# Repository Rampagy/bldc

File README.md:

# bldc

Open source brushless direct current (permanent magnet alternating current) hardware and software.

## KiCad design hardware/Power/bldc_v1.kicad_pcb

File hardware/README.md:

# Kicad

Version 5.1.2

## Setup

Set Environment Variable `KILOCALLIB` to `path/to/bldc/hardware`.  This allows Kicad to find the custom schematic and footprint libraries:

* infineon.lib
* Interface_RS485.lib
* STM32F4-DISCOVERY-SIMON.lib
* custom.pretty

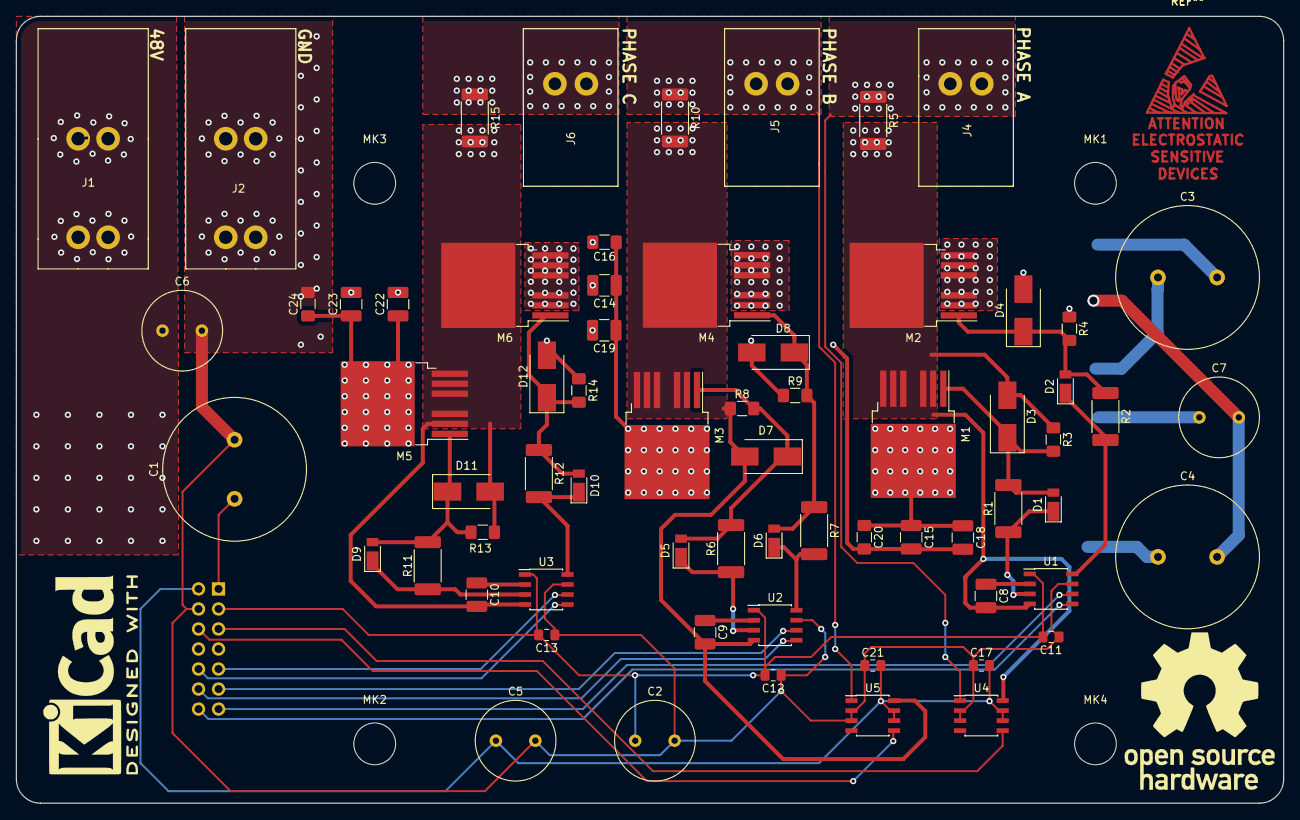
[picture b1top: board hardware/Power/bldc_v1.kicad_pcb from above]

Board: 2 copper layers, 160.8 x 99.8 mm, 72 parts (1 on the bottom side), 33 nets.

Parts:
C1, C3, C4: 680uF; C_Radial_D18.0mm_H35.5mm_P7.50mm
C2, C5, C6, C7: 100uF; C_Radial_D10.0mm_H20.0mm_P5.00mm
C8, C9, C10: 0.68u; C_1210_3225Metric_Pad1.42x2.65mm_HandSolder
C11, C12, C13: 10.0u; C_0805_2012Metric_Pad1.15x1.40mm_HandSolder
C14, C15, C18, C19, C22, C23: 4.7uF; C_1210_3225Metric_Pad1.42x2.65mm_HandSolder
C16, C20, C24: 2.2uF; C_1206_3216Metric_Pad1.42x1.75mm_HandSolder
C17, C21: 10.0uF; R_0805_2012Metric_Pad1.15x1.40mm_HandSolder
D1, D2, D5, D6, D9, D10: DFLS1100DICT-ND; D_PowerDI-123
D3, D4, D7, D8, D11, D12: SMBJ14A-FDICT-ND; D_SMB_Handsoldering
J1, J2: Screw_Terminal_01x01; Weidmuller 85amps
J3: Conn_02x07_Counter_Clockwise; PinHeader_2x07_P2.54mm_Vertical
J4, J5, J6: Screw_Terminal_01x01; Pheonix 65amps
M1, M2, M3, M4, M5, M6: IPB017N10N5; TO-263-6
MK1, MK2, MK3, MK4: Mounting_Hole; MountingHole_5.3mm_M5_DIN965
R1, R2, R6, R7, R11, R12: 10; R_2512_6332Metric_Pad1.52x3.35mm_HandSolder
R3, R4, R8, R9, R13, R14: 20k; R_1206_3216Metric_Pad1.42x1.75mm_HandSolder
R5, R10, R15: 0.001; R_2512_6332Metric_Pad1.52x3.35mm_HandSolder
U1, U2, U3: UCC27211A; SOIC-8_3.9x4.9mm_P1.27mm
U4, U5: AD8410; SOIC-8_3.9x4.9mm_P1.27mm

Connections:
/5v: C5.1, C17.2, C21.2, J3.2, U4.6, U4.7, U5.6, U5.7
/12v: C2.1, C11.2, C12.2, C13.2, J3.3, U1.1, U2.1, U3.1
/48v: C1.1, C3.1, C4.1, C6.1, C7.1, C14.1, C15.1, C16.1, C18.1, C19.1, C20.1, C22.1, C23.1, C24.1, J1.1, J3.1, M1.4, M3.4, M5.4
/GND: C1.2, C2.2, C3.2, C4.2, C5.2, C6.2, C7.2, C11.1, C12.1, C13.1, C14.2, C15.2, C16.2, C17.1, C18.2, C19.2, C20.2, C21.1, C22.2, C23.2, C24.2, D4.2, D8.2, D12.2, J2.1, J3.4, M2.2, M2.3, M2.5, M2.6, M2.7, M4.2, M4.3, M4.5, M4.6, M4.7, M6.2, M6.3, M6.5, M6.6, M6.7, R4.1, R9.1, R14.1, U1.7, U2.7, U3.7, U4.2, U4.3, U5.2, U5.3
/HS_A_TTL_PWM: J3.14, U1.5
/HS_B_TTL_PWM: J3.12, U2.5
/HS_C_TTL_PWM: J3.10, U3.5
/LS_A_TTL_PWM: J3.13, U1.6
/LS_B_TTL_PWM: J3.11, U2.6
/LS_C_TTL_PWM: J3.9, U3.6
/PHASEA_FB: J3.5, U4.5
/PHASEB_FB: J3.6, U5.5
/PHASE_A: J4.1, R5.1, U4.1
/PHASE_B: J5.1, R10.1, U5.1
/PHASE_C: J6.1, R15.1
/gatedrivers/HO_A: D1.1, R1.2, U1.3
/gatedrivers/HO_B: D5.1, R6.2, U2.3
/gatedrivers/HO_C: D9.1, R11.2, U3.3
/gatedrivers/LO_A: D2.1, R2.2, U1.8
/gatedrivers/LO_B: D6.1, R7.2, U2.8
/gatedrivers/LO_C: D10.1, R12.2, U3.8
/gatedrivers/PHASEA_SOURCE: C8.2, D3.2, M1.2, M1.3, M1.5, M1.6, M1.7, M2.4, R3.1, R5.2, U1.4, U4.8
/gatedrivers/PHASEB_SOURCE: C9.2, D7.2, M3.2, M3.3, M3.5, M3.6, M3.7, M4.4, R8.1, R10.2, U2.4, U5.8
/gatedrivers/PHASEC_SOURCE: C10.2, D11.2, M5.2, M5.3, M5.5, M5.6, M5.7, M6.4, R13.1, R15.2, U3.4
/mosfets/HS_A_GATE: D1.2, D3.1, M1.1, R1.1, R3.2
unnamed: C8.1, U1.2
unnamed: C9.1, U2.2
unnamed: C10.1, U3.2
unnamed: D2.2, D4.1, M2.1, R2.1, R4.2
unnamed: D5.2, D7.1, M3.1, R6.1, R8.2
unnamed: D6.2, D8.1, M4.1, R7.1, R9.2
unnamed: D10.2, D12.1, M6.1, R12.1, R14.2
unnamed: D9.2, D11.1, M5.1, R11.1, R13.2

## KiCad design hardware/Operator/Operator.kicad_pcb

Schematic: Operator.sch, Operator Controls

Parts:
A1: Arduino_UNO_R3
C1, C2: 100uF; CP_Radial_D10.0mm_P5.00mm
C3: 2.2uF; C_1206_3216Metric_Pad1.42x1.75mm_HandSolder
J1: RJ45; RJ45_Amphenol_54602-x08_Horizontal
J2: Screw_Terminal_01x02; TerminalBlock_Phoenix_MKDS-1,5-2_1x02_P5.00mm_Horizontal
J3: Conn_01x06_Male; PinHeader_1x06_P2.54mm_Vertical
R1, R2: 120; R_0805_2012Metric_Pad1.33x1.40mm_HandSolder
R3: 2k; R_0805_2012Metric_Pad1.33x1.40mm_HandSolder
R4, R5, R6, R7: 680; R_0805_2012Metric_Pad1.33x1.40mm_HandSolder
U1: DS89C21; SOIC-8_3.9x4.9mm_P1.27mm

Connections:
/5v: A1.5, C1.1, C2.1, C3.1, J1.3, J2.1, J3.2, R4.1, R6.1, U1.1
/+RX: J1.2, R1.1, R4.2, U1.8
/+Tx: J1.7, R2.1, R6.2, U1.6
/-RX: J1.1, R1.2, R5.1, U1.7
/-TX: J1.8, R2.2, R7.1, U1.5
/A0: A1.9, J2.2, R3.1
/A4: A1.13, J3.4
/A5: A1.14, J3.3
/D3: A1.18, J3.6
/D5: A1.20, J3.5
/GND: A1.6, A1.7, A1.29, C1.2, C2.2, C3.2, J1.6, J3.1, R3.2, R5.2, R7.2, U1.4
/TransEnable_TTL: A1.17, J1.5
/USART_RX: A1.15, U1.2
/USART_TX: A1.16, U1.3

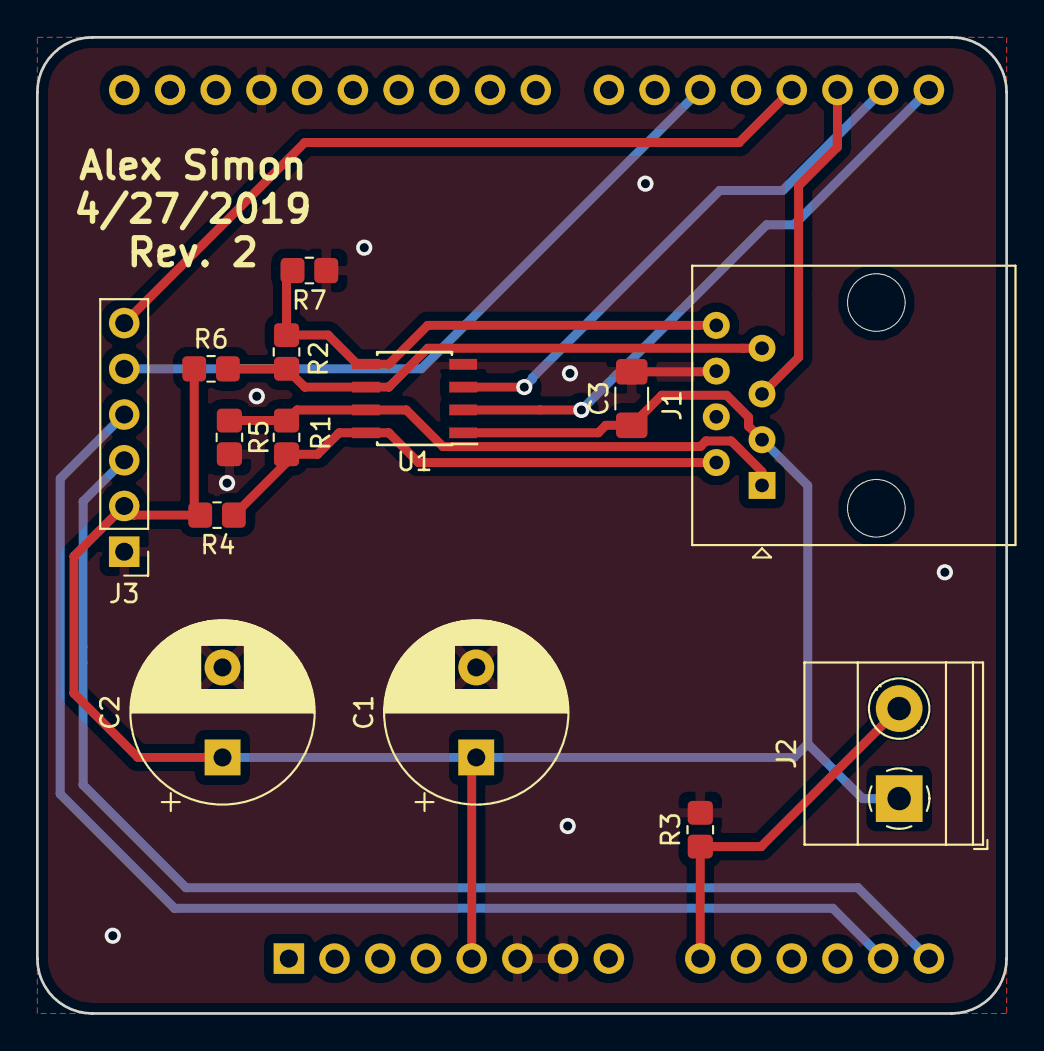
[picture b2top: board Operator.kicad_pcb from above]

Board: 2 copper layers, 53.8 x 54.2 mm, 15 parts (1 on the bottom side), 14 nets.

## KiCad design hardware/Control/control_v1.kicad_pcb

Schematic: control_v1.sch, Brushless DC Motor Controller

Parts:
C12: 2.2uF; C_1206_3216Metric_Pad1.42x1.75mm_HandSolder
J1: Conn_02x07_Counter_Clockwise; PinHeader_2x07_P2.54mm_Vertical
J2: Screw_Terminal_01x05; TerminalBlock_Phoenix_MKDS-1,5-5-5.08_1x05_P5.08mm_Horizont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
J4: RJ45; RJ45_Amphenol_54602-x08_Horizontal
MK1, MK2, MK3, MK4: Mounting_Hole; MountingHole_5.3mm_M5_DIN965_Pad
R17, R18: 120; R_0805_2012Metric_Pad1.33x1.40mm_HandSolder
U3: DS89C21; SOIC-8_3.9x4.9mm_P1.27mm

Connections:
/5v: C12.1, J1.2, J2.5, J4.3, U3.1; also elsewhere on the board
/12v: J1.3; also elsewhere on the board
/48v: J1.1; also elsewhere on the board
/+RX: J4.7, R17.1, U3.8
/+TX: J4.2, R18.1, U3.6
/-RX: J4.8, R17.2, U3.7
/-TX: J4.1, R18.2, U3.5
/AUX_0: J1.7; also elsewhere on the board
/AUX_1: J1.8; also elsewhere on the board
/GND: C12.2, J1.4, J2.4, J4.6, MK1.1, MK2.1, MK3.1, MK4.1, U3.4; also elsewhere on the board
/HALL_A: J2.3; also elsewhere on the board
/HALL_B: J2.2; also elsewhere on the board
/HALL_C: J2.1; also elsewhere on the board
/HS_A_TTL_PWM: J1.14; also elsewhere on the board
/HS_B_TTL_PWM: J1.12; also elsewhere on the board
/HS_C_TTL_PWM: J1.10; also elsewhere on the board
/LS_A_TTL_PWM: J1.13; also elsewhere on the board
/LS_B_TTL_PWM: J1.11; also elsewhere on the board
/LS_C_TTL_PWM: J1.9; also elsewhere on the board
/PHASEA_FB: J1.5; also elsewhere on the board
/PHASEB_FB: J1.6; also elsewhere on the board
/TransEnable_TTL: J4.5; also elsewhere on the board
/USART_RX: U3.2; also elsewhere on the board
/USART_TX: U3.3; also elsewhere on the board

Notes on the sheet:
Connections
Mounting Holes

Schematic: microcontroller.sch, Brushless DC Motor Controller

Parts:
C7, C8, C9, C10, C11: 2.2nF; C_0805_2012Metric_Pad1.33x1.40mm_HandSolder
M1: STM32F4-DISCOVERY; STM32-F4-DISCOVERY
R5, R8: 680; R_0805_2012Metric_Pad1.33x1.40mm_HandSolder
R6, R7: 2.0k; R_0805_2012Metric_Pad1.33x1.40mm_HandSolder
R9, R11, R13: 18k; R_0805_2012Metric_Pad1.33x1.40mm_HandSolder
R10, R12, R14: 30k; R_0805_2012Metric_Pad1.33x1.40mm_HandSolder

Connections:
/5v: M1.53, M1.54; also elsewhere on the board
/AUX_0: M1.11; also elsewhere on the board
/AUX_1: M1.9; also elsewhere on the board
/GND: C7.2, C8.2, C9.2, C10.2, C11.2, M1.1, M1.2, M1.5, M1.23, M1.49, M1.50, M1.51, M1.52, M1.99, M1.100, R6.2, R7.2, R10.2, R12.2, R14.2; also elsewhere on the board
/HALL_A: R13.2; also elsewhere on the board
/HALL_B: R11.2; also elsewhere on the board
/HALL_C: R9.2; also elsewhere on the board
/HS_A_TTL_PWM: M1.27; also elsewhere on the board
/HS_B_TTL_PWM: M1.29; also elsewhere on the board
/HS_C_TTL_PWM: M1.31; also elsewhere on the board
/LS_A_TTL_PWM: M1.26; also elsewhere on the board
/LS_B_TTL_PWM: M1.28; also elsewhere on the board
/LS_C_TTL_PWM: M1.30; also elsewhere on the board
/PHASEA_FB: R8.1; also elsewhere on the board
/PHASEB_FB: R5.1; also elsewhere on the board
/USART_RX: M1.41; also elsewhere on the board
/USART_TX: M1.40; also elsewhere on the board
/microcontroller/HALL_A_SENSE: C9.1, M1.75, R13.1, R14.1
/microcontroller/HALL_B_SENSE: C8.1, M1.76, R11.1, R12.1
/microcontroller/HALL_C_SENSE: C7.1, M1.22, R9.1, R10.1
/microcontroller/PC4: C11.1, M1.20, R7.1, R8.2
/microcontroller/PC5: C10.1, M1.19, R5.2, R6.1

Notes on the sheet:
STM uses 2x25 0.1" female headers on each side PN: SAM10038-ND
Signal Filtering

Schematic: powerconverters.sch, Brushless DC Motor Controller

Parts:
C1, C2: 100uF; CP_Radial_D10.0mm_P5.00mm
C3: 330uF; CP_Radial_D10.0mm_P5.00mm
C4: 1.2mF; CP_Radial_D10.0mm_P5.00mm
C5, C6: 2.2uF; C_1206_3216Metric_Pad1.42x1.75mm_HandSolder
D1, D2: 1N5819; D_DO-41_SOD81_P12.70mm_Horizontal
L1: 680uH; L_Bourns_SRR1260
L2: 330uH; L_Bourns_SRR1260
Q1: BCX56; SOT-89-3
R1, R16: 18k; R_0805_2012Metric_Pad1.33x1.40mm_HandSolder
R2, R4: 2k; R_0805_2012Metric_Pad1.33x1.40mm_HandSolder
R3, R15: 6k; R_0805_2012Metric_Pad1.33x1.40mm_HandSolder
R19: 680; R_0805_2012Metric_Pad1.33x1.40mm_HandSolder
U1, U2: TL2575HV-ADJ; TO-263-5_TabPin3

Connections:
/5v: C4.1, L2.2, R3.1; also elsewhere on the board
/12v: C3.1, L1.2, R1.1; also elsewhere on the board
/48v: C1.1, C2.1, C5.1, C6.1, R16.1, U1.1, U2.1; also elsewhere on the board
/GND: C1.2, C2.2, C3.2, C4.2, C5.2, C6.2, D1.2 (A), D2.2 (A), Q1.3, R2.2, R4.2, R15.2, U1.3, U2.3, U2.5; also elsewhere on the board
/TransEnable_TTL: R19.2; also elsewhere on the board
/powerconverters/5v_FB: R3.2, R4.1, U2.4
/powerconverters/5v_OUT: D2.1 (K), L2.1, U2.2
/powerconverters/12v_FB: R1.2, R2.1, U1.4
/powerconverters/12v_OUT: D1.1 (K), L1.1, U1.2
/powerconverters/TransEnable: Q1.2, R16.2, U1.5
unnamed: Q1.1, R15.1, R19.1

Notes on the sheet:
12v Converter
5v Converter
Transmission Enable

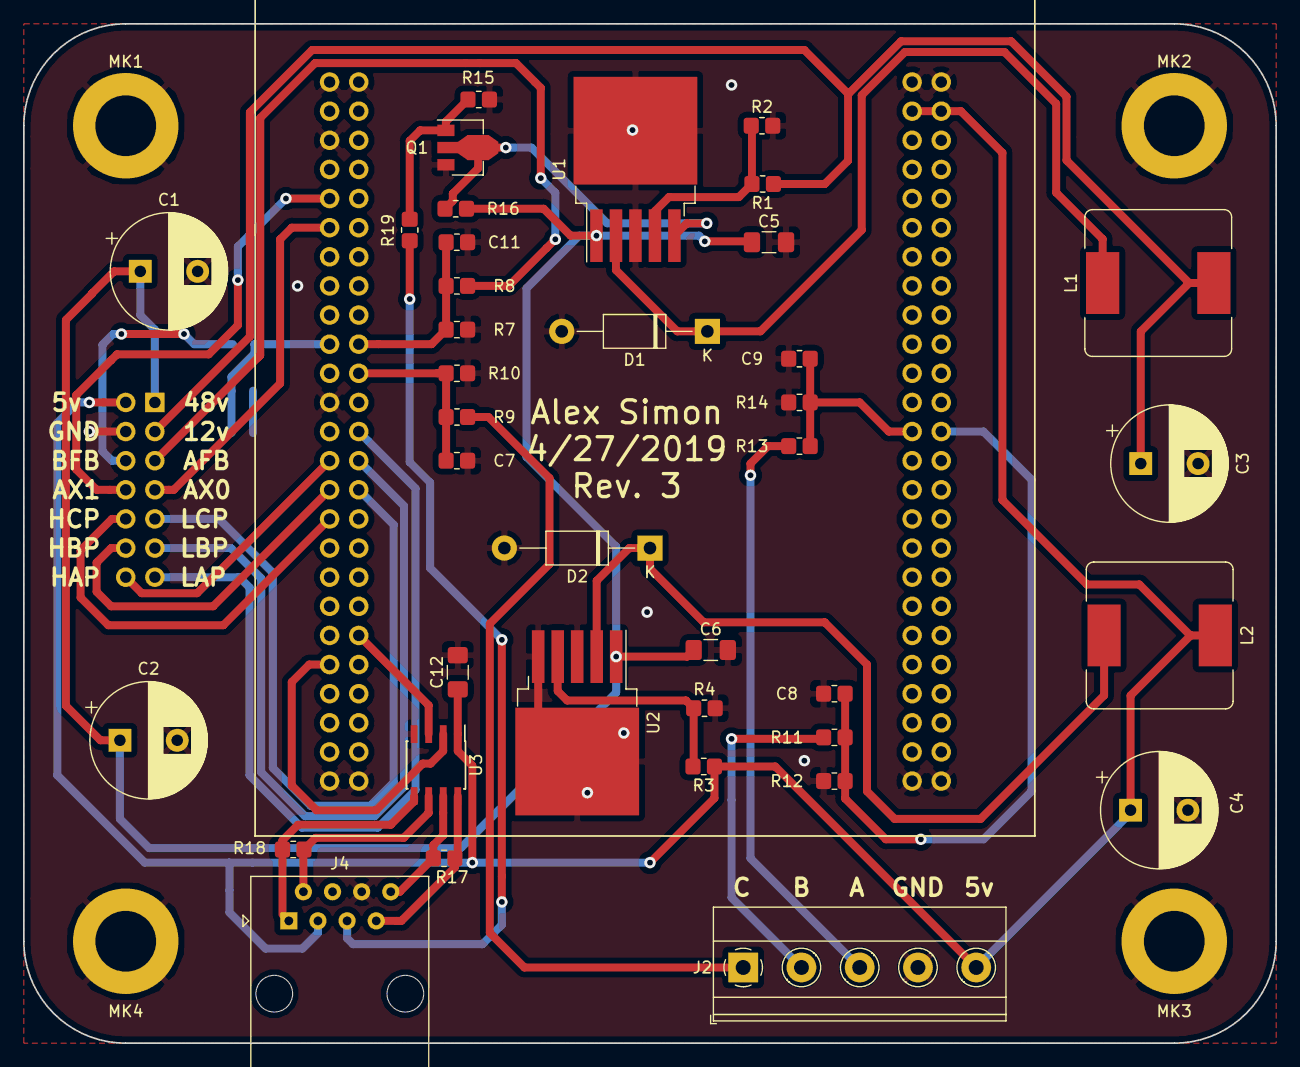
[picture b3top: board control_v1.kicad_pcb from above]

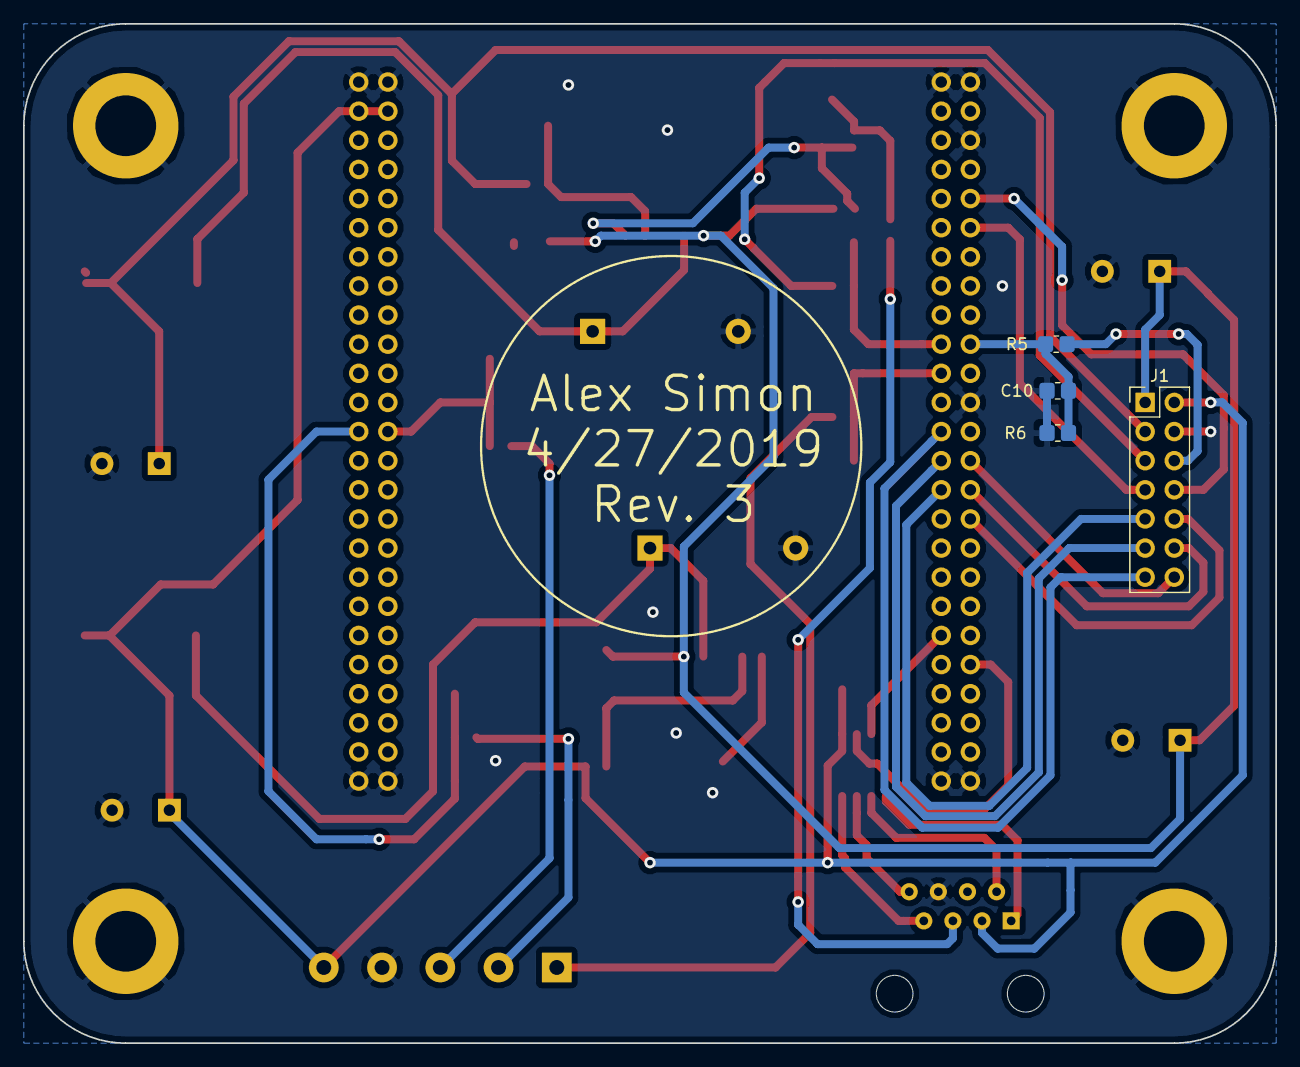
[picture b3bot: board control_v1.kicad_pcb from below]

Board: 2 copper layers, 109.2 x 88.9 mm, 47 parts (4 on the bottom side), 35 nets.

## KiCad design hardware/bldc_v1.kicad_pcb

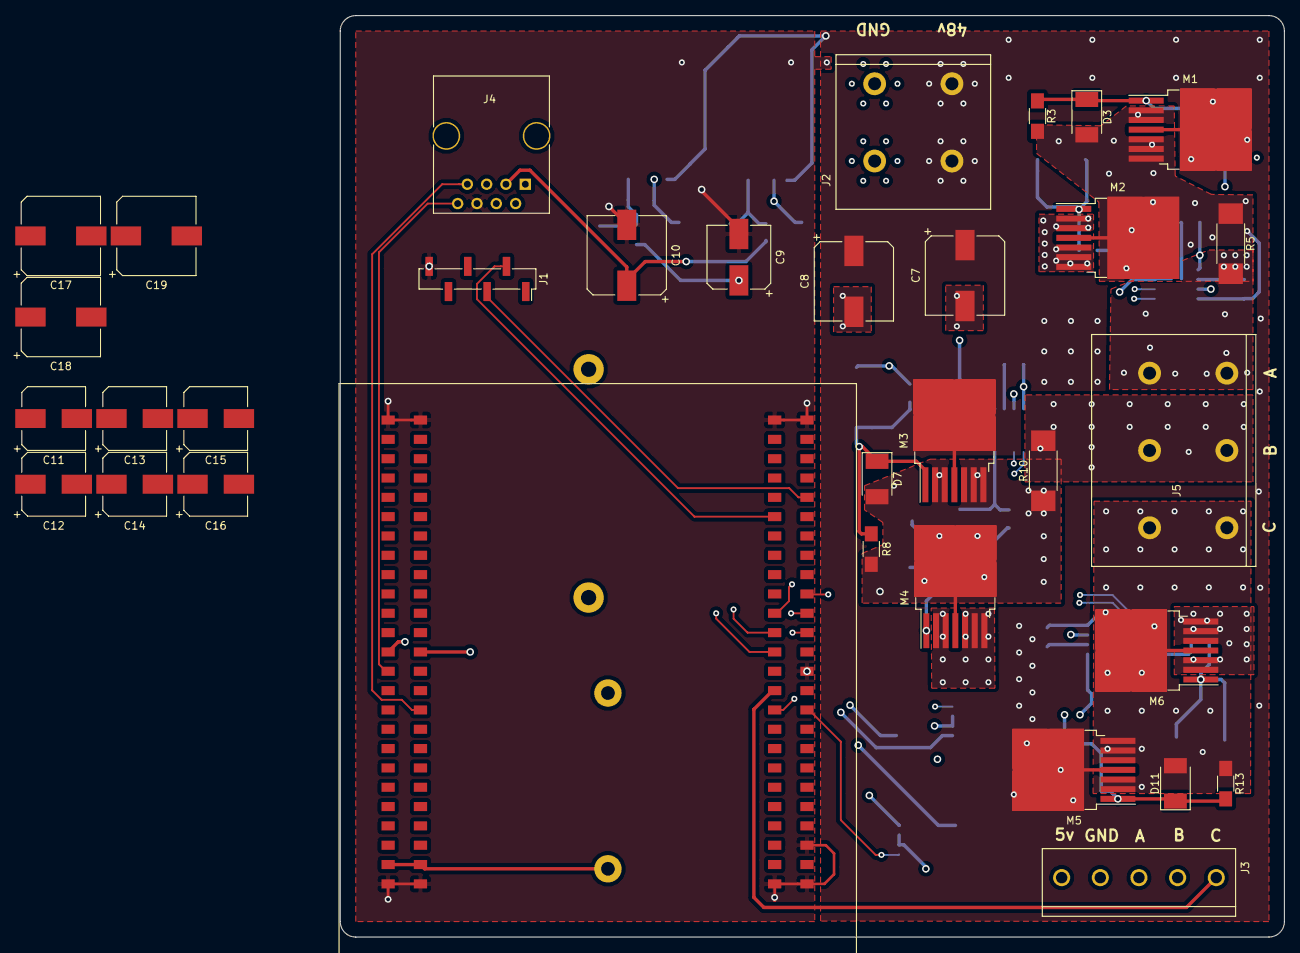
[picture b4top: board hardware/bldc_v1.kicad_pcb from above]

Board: 4 copper layers, 124.1 x 121.1 mm, 72 parts (0 on the bottom side), 43 nets.

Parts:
5vConverter1, 12vConverter1: TL2575HV; TO-263-5_TabPin3
C1, C2, C3: 0.68u; C_0805_HandSoldering
C4, C5, C6: 10.0u; C_0805_HandSoldering
C7, C8: 100uF; CP_Elec_10x10
C9: 330uF; CP_Elec_8x10
C10: 1200uF; CP_Elec_10x10
C11, C12, C13, C14, C15, C16: 4.7u; CP_Elec_8x6.5
C17, C18, C19: 100u; CP_Elec_10x10
D1, D2, D5, D6, D9, D10: DFLS1100-7; D_PowerDI-123
D3, D4, D7, D8, D11, D12: SMBJ14A-13-F; D_2114
D13, D14: NRVTS260ESFT1G; D_SOD-123F
J1: Conn_01x06; Pin_Header_Straight_1x06_Pitch2.54mm_SMD_Pin1Right
J2: 1x2_ScrewTerminal_65A
J3: Screw_Terminal_01x05; 1x5_ScrewTerminal_1A
J4: RJ45; RJ45_8
J5: Screw_Terminal_01x03; 1x3_ScrewTerminal_65A
L1: 680uH; L_Toroid_Horizontal_D32.5mm_P30.00mm_Bourns_2300
L2: 330uH; L_Toroid_Horizontal_D24.1mm_P23.10mm_Bourns_2200
M1, M2, M3, M4, M5, M6: IPB017N10N5; TO-263-7_TabPin4
M7: STM32F4-DISCOVERY; STM32-F4-DISCOVERY
PhaseA1: UCC27211A; Infineon_PG-DSO-8-43
PhaseB1: UCC27211A; Infineon_PG-DSO-8-43
PhaseC1: UCC27211A; Infineon_PG-DSO-8-43
R1, R2, R6, R7, R11, R12: 10; R_2512_HandSoldering
R3, R4, R8, R9, R13, R14: 20k; R_1206_HandSoldering
R5, R10: 0.001; R_2512_HandSoldering
R15: 18k; R_0805_HandSoldering
R16, R18: 2k; R_0603_HandSoldering
R17: 6.04k; R_0603_HandSoldering
U1, U2: AD8205; SO-8_5.3x6.2mm_Pitch1.27mm

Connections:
/5v: C10.1, J3.5, J4.3, L2.2, M7.53, M7.54, R17.1, U1.6, U1.7, U2.6, U2.7
/48v: 5vConverter1.1, 12vConverter1.1, C7.1, C8.1, C11.1, C12.1, C13.1, C14.1, C15.1, C16.1, C17.1, C18.1, C19.1, J2.2, J2.4, M1.4, M3.4, M5.4
/FB_A: M7.20, U1.5
/FB_B: M7.19, U2.5
/GND: 5vConverter1.3, 5vConverter1.5, 12vConverter1.3, 12vConverter1.5, C4.1, C5.1, C6.1, C7.2, C8.2, C9.2, C10.2, C11.2, C12.2, C13.2, C14.2, C15.2, C16.2, C17.2, C18.2, C19.2, D4.2, D8.2, D12.2, D13.2, D14.2, J1.6, J2.1, J2.3, J3.4, J4.6, M2.2, M2.3, M2.5, M2.6, M2.7, M4.2, M4.3, M4.5, M4.6, M4.7, M6.2, M6.3, M6.5, M6.6, M6.7, M7.1, M7.2, M7.5, M7.23, M7.49, M7.50, M7.51, M7.52, M7.99, M7.100, PhaseA1.7, PhaseA1.9, PhaseB1.7, PhaseB1.9, PhaseC1.7, PhaseC1.9, R4.1, R9.1, R14.1, R16.2, R18.2, U1.2, U1.3, U2.2, U2.3
/GateDriver/+12V: C4.2, C5.2, C6.2, C9.1, L1.2, PhaseA1.1, PhaseB1.1, PhaseC1.1, R15.1
/GateDriver/HS_A_GATE: D1.1, PhaseA1.3, R1.2
/GateDriver/HS_A_TTL_PWM: M7.27, PhaseA1.5
/GateDriver/HS_B_GATE: D5.1, PhaseB1.3, R6.2
/GateDriver/HS_B_TTL_PWM: M7.29, PhaseB1.5
/GateDriver/HS_C_GATE: D9.1, PhaseC1.3, R11.2
/GateDriver/HS_C_TTL_PWM: M7.31, PhaseC1.5
/GateDriver/LS_A_GATE: D2.1, PhaseA1.8, R2.2
/GateDriver/LS_A_TTL_PWM: M7.26, PhaseA1.6
/GateDriver/LS_B_GATE: D6.1, PhaseB1.8, R7.2
/GateDriver/LS_B_TTL_PWM: M7.28, PhaseB1.6
/GateDriver/LS_C_GATE: D10.1, PhaseC1.8, R12.2
/GateDriver/LS_C_TTL_PWM: M7.30, PhaseC1.6
/GateDriver/PhaseASource: C3.2, D3.2, M1.2, M1.3, M1.5, M1.6, M1.7, M2.4, PhaseA1.4, R3.2, R5.1, U1.8
/GateDriver/PhaseBSource: C1.2, D7.2, M3.2, M3.3, M3.5, M3.6, M3.7, M4.4, PhaseB1.4, R8.1, R10.1, U2.8
/MOSFETS/PhaseA: J5.1, R5.2, U1.1
/MOSFETS/PhaseB: J5.2, R10.2, U2.1
/MOSFETS/PhaseC: C2.2, D11.2, J5.3, M5.2, M5.3, M5.5, M5.6, M5.7, M6.4, PhaseC1.4, R13.1
/Microcontroller/HALL_A: J3.3, M7.75
/Microcontroller/HALL_B: J3.2, M7.76
/Microcontroller/HALL_C: J3.1, M7.22
/Microcontroller/I2C_SCL: J4.7, M7.69
/Microcontroller/I2C_SDA: J4.8, M7.74
/Microcontroller/USART_RX: J1.3, M7.41
/Microcontroller/USART_TX: J1.2, M7.40
unnamed: 5vConverter1.2, D14.1, L2.1
unnamed: 5vConverter1.4, R17.2, R18.1
unnamed: 12vConverter1.2, D13.1, L1.1
unnamed: 12vConverter1.4, R15.2, R16.1
unnamed: C1.1, PhaseB1.2
unnamed: C2.1, PhaseC1.2
unnamed: C3.1, PhaseA1.2
unnamed: D1.2, D3.1, M1.1, R1.1, R3.1
unnamed: D2.2, D4.1, M2.1, R2.1, R4.2
unnamed: D5.2, D7.1, M3.1, R6.1, R8.2
unnamed: D6.2, D8.1, M4.1, R7.1, R9.2
unnamed: D10.2, D12.1, M6.1, R12.1, R14.2
unnamed: D9.2, D11.1, M5.1, R11.1, R13.2

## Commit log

2018-03-16 Initial folder setup
2018-03-16 setup initial project
2018-03-18 Added mosfet circuit
2018-03-19 Updaated Driver section
2018-03-19 removing unnecesary file
2018-03-20 Update gate driver protection
2018-03-23 Added power converters
2018-03-25 added microcontroller page
2018-03-25 cleaned up schematic
2018-03-25 removed unnecessary file
2018-03-25 associated footprints
2018-03-25 annotated schematic
2018-03-25 Added netlist
2018-03-29 created new footprints, modified schematic
2018-03-29 created new net
2018-03-29 dispersed condensed intitial pcb layout
2018-03-30 layed parts out on board
2018-03-30 added updated schematic
2018-04-04 finished board layout
2018-04-04 added text on silk screen
2019-01-25 updated board layout
2019-01-25 updated part numbers
2019-01-26 Converted to kicad 5
2019-01-26 updated net, sch. removed old board layout
2019-01-26 Initial Board layout
2019-01-27 routed phase A power electronics
2019-01-27 routed phase B power electronics
2019-01-27 Completed routing
2019-01-28 Added additional planes for extra current
2019-01-29 updated routing and all plots
2019-01-31 Updated schematic for additional capacitors
2019-01-31 Added additional capacitors for 48v bus
2019-02-02 completely restarted
2019-02-02 rearranged files
2019-02-02 rearranged libraries
2019-02-02 added mounting holes and updates schematic areas
2019-02-02 Added control schematic
2019-02-03 Added capacitor to 5v bus on power board
2019-02-03 committing current state of report
2019-02-04 Added gate driver section
2019-02-04 updated margins
2019-02-05 updated schematic with voltage divider
2019-02-08 updated schematics, added shoot through protection
2019-02-09 removed shootthourgh protection
2019-02-09 Added footprints for each component
2019-02-10 Added auxilary components
2019-02-10 started board layout
2019-02-13 Added filter components and baord layout
2019-02-13 Added pdf for board layout
2019-02-13 Added color pdf
2019-02-14 Laid all traces, updated documentation
2019-02-19 Added drill files
2019-02-21 Adding additinal info to report
2019-02-22 Wrote section on 5v converter
2019-03-09 Updated to rev 2
2019-03-16 Added Transmission Enable
2019-03-21 Added RS485 differential pair
2019-03-21 Adding arduino board
2019-03-21 Updated schematic for termination resistors
2019-03-22 Added termination resistors
2019-03-22 Adding 0.1" pin headers
2019-03-22 Added gerber files
2019-03-23 Updated Gerber files
2019-03-27 Added decoupling cap for rs485 chip
2019-03-27 Added decoupling cap for RS485
2019-03-27 Updated decoupling capacitor value
2019-03-27 Added mask
2019-03-27 Created silk screen
2019-04-16 Addedcurrent limiting resistor, increased 2.2uF cap footprint
2019-04-17 Updated footprint size, put arduino on opposite side of board.
2019-04-23 Setting up folder structure
2019-04-23 Adding peripheral files
2019-04-23 Adding read me
2019-04-24 Removed and added files until all errors were gone
2019-04-26 Added delay and preprocessor defines
2019-04-27 Added RS485 bias resistors
2019-04-27 Updated silk screen
2019-04-27 Updated Documentation
2019-04-28 Tuned delay for ms resolution
2019-04-29 Hall effect working with USART output
2019-04-30 Added TIM9 interrupt
2019-05-01 Removed voltage biasing resistors from control board
2019-05-01 Added 10ms debug data
2019-05-04 Got full duplex action
2019-05-05 Added RS485 Rx Delay timeout
2019-05-05 Added 10ms task to arduino code
2019-05-08 Update voltage divider on 12v enable transistor
2019-05-08 Made arduino holes bigger
2019-05-11 Full duplex communication
2019-05-11 Updated debug LEDs
2019-05-20 Adding interrupt priority updates
2019-05-21 Added slew to 25% throttle
2019-06-06 Adding 12v toggle
2019-06-06 Scheduled debug to be sent after Rx to avoid overruns
2019-06-11 Adding license
2019-06-14 Added complementary PWM
2019-06-17 Fixing polarity
2019-06-18 Fixing dead time
2019-06-18 Updated orange LED functionality
2019-06-18 Updated slew and orange LED functionality
2019-06-18 Updated Timers
2019-06-19 Trying design of experiments to figure out complementary PWM
2019-06-19 updating design of experiments
2019-06-20 Updated PWM output
2019-07-06 Added Motor control theory
2019-07-07 Added phase advance logic
2019-07-07 Added release configuration
2019-07-09 Fixed PHASE_PREDICTION bug
2019-07-13 Created relative path for library
2019-07-13 updated to kciad projects to 5.1.2
2019-07-13 Added readme
2019-09-07 Updating schematic
2019-09-07 Added Footprints
2019-09-11 Updating footprints
2019-09-11 Updating readme
2019-09-14 Updating schematic with new footprints
2019-09-14 Adding new footprints
2019-09-14 Added more capacitance
2019-09-21 Adding communication library
2019-10-26 Updated operator station
2019-10-26 REmoved redundant functions from library
2019-10-27 Updated RS485 RX driver
2019-10-28 Fixed 2 byte RS485 receives
2019-10-28 Set baudrate, fixed PWM calculations
2019-10-28 Added moving average filter for speed
2019-10-30 Updated RS485 driver to be more robust
2019-11-02 Updated Speed Sensor and UART driver
2019-11-05 Updating Operator Rx
2019-11-05 Fixing UART Rx bug
2019-11-11 Updating motor control
2019-11-17 Added fast enable
2019-11-18 Added internal max slew limit
2021-10-28 Adding README
2021-10-28 Adding more to the report
2021-10-30 Updating report
2022-12-08 Adding parts list
2022-12-15 Adding proper pdf
